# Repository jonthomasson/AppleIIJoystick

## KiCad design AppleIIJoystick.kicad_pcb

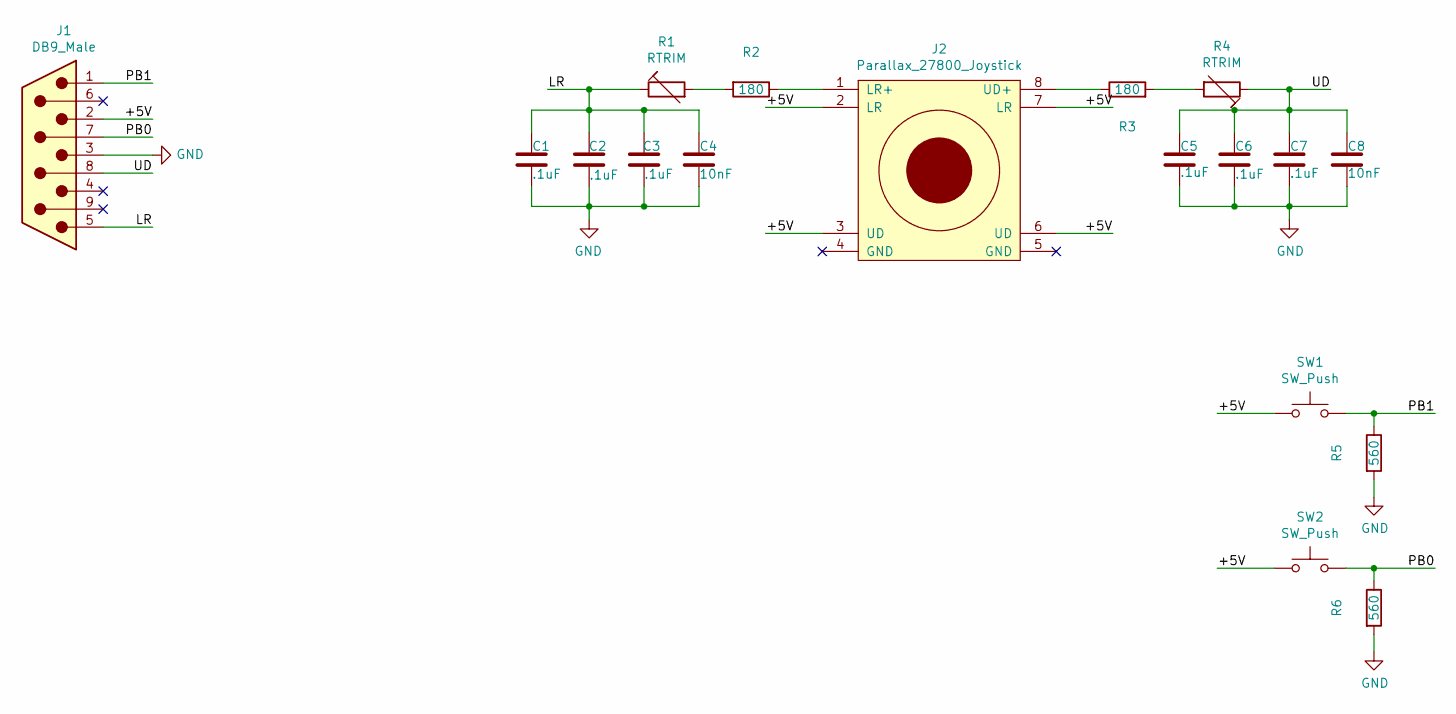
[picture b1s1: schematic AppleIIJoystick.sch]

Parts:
C1, C2, C3, C5, C6, C7: .1uF; C_Disc_D3.0mm_W2.0mm_P2.50mm
C4, C8: 10nF; C_Disc_D3.0mm_W2.0mm_P2.50mm
J1: DB9_Male; ADS09_DB9
J2: Parallax_27800_Joystick
R1, R4: RTRIM; PT10LV10_TRIM_POT
R2, R3: 180; R_Axial_DIN0207_L6.3mm_D2.5mm_P10.16mm_Horizontal
R5, R6: 560; R_Axial_DIN0207_L6.3mm_D2.5mm_P10.16mm_Horizontal
SW1, SW2: SW_Push; ESWITCH_E11GRY_BTN

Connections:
/+5V: J1.2, J2.2 (LR), J2.3 (UD), J2.6 (UD), J2.7 (LR), SW1.1, SW2.1
/LR: C1.1, C2.1, C3.1, C4.1, J1.5, R1.1
/PB0: J1.7, R6.1, SW2.3
/PB1: J1.1, R5.1, SW1.3
/UD: C5.1, C6.1, C7.1, C8.1, J1.8, R4.1
GND: C1.2, C2.2, C3.2, C4.2, C5.2, C6.2, C7.2, C8.2, J1.3, R5.2, R6.2
unnamed: J2.1 (LR+), R2.1
unnamed: J2.8 (UD+), R3.1
unnamed: R1.2, R2.2
unnamed: R3.2, R4.2

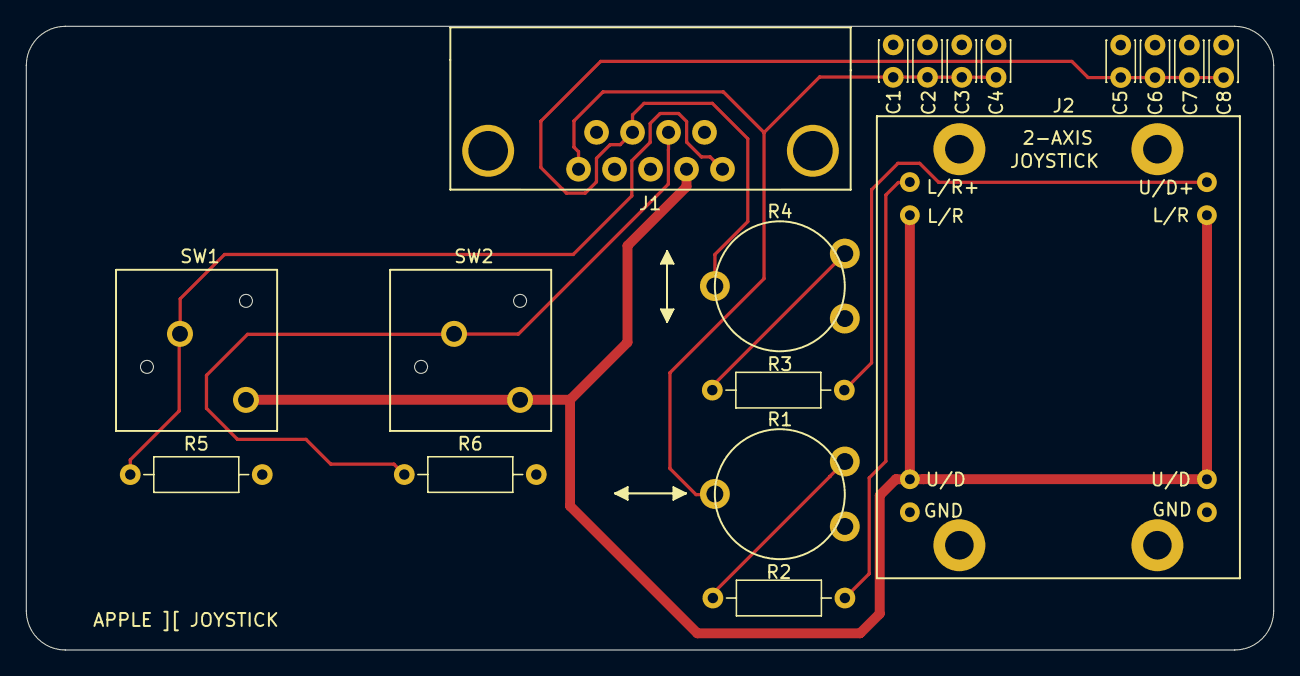
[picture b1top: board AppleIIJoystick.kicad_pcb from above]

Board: 2 copper layers, 96.0 x 48.0 mm, 18 parts (0 on the bottom side), 10 nets.

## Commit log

2019-11-08 :octocat: Added .gitattributes & .gitignore files
2019-11-08 finished schematic
2019-11-09 starting footprint/3d models
2019-11-09 finishing up parallax 27800 joystick footprint/3d model
2019-11-10 db9 footprint/3d model created
2019-11-10 added x,y trim pot and imported net list
2019-11-11 swapped out buttons. new footprint/3d model.
2019-11-12 adding edge cuts layer and board outline
2019-11-13 board layout
2019-11-14 finished routing pcb
2019-11-15 added gerber
2019-11-15 made some modifications to ground pour and new gerber
